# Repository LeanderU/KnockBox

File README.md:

# KnockBox

Want to stay in contact with your friends, family, or partner over long distances? The KnockBox was created to foster a sense of proximity to them. Instead of physically knocking on their door, you can knock on your box, and theirs will imitate your physical knocking. Additionally, the pair of identical boxes can exchange short audio messages, similar to Walkie Talkies.  

## How it works:

This project focuses on an interactive device that communicates with identical boxes, independent of their locations. The boxes are connected via the Internet, allowing them to exchange knocking sounds and audio messages. A servo imitates the physical knocking coming from a user of another box, while an LED indicates if a new audio message has been received. The user interface is limited to only one button that's used for playing the received audio message, recording a message, and sending it.

## Repository Contents:

1. **Docs**: Contains the Product Brief and Project Requirements.
2. **Electrical**: Includes schematics and PCB design files.
3. **Software**: Contains testing of submodules.

*Please note that the code of the final KnockBox and documentation on the hardware development are still under revision and have not yet been included in this repository.*

https://github.com/LeanderU/KnockBox/assets/84909019/8b67ddaa-3543-461e-bd95-6ebf5e21cfc9

The video shown only demonstrates the ability to record and play the knocking sound. The capability of recording and replaying audio messages is not implemented yet.

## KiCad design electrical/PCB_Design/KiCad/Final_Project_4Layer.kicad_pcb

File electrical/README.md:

After Assembly:

Screenshot from KiCad before the files were sent to the Manufacturer:

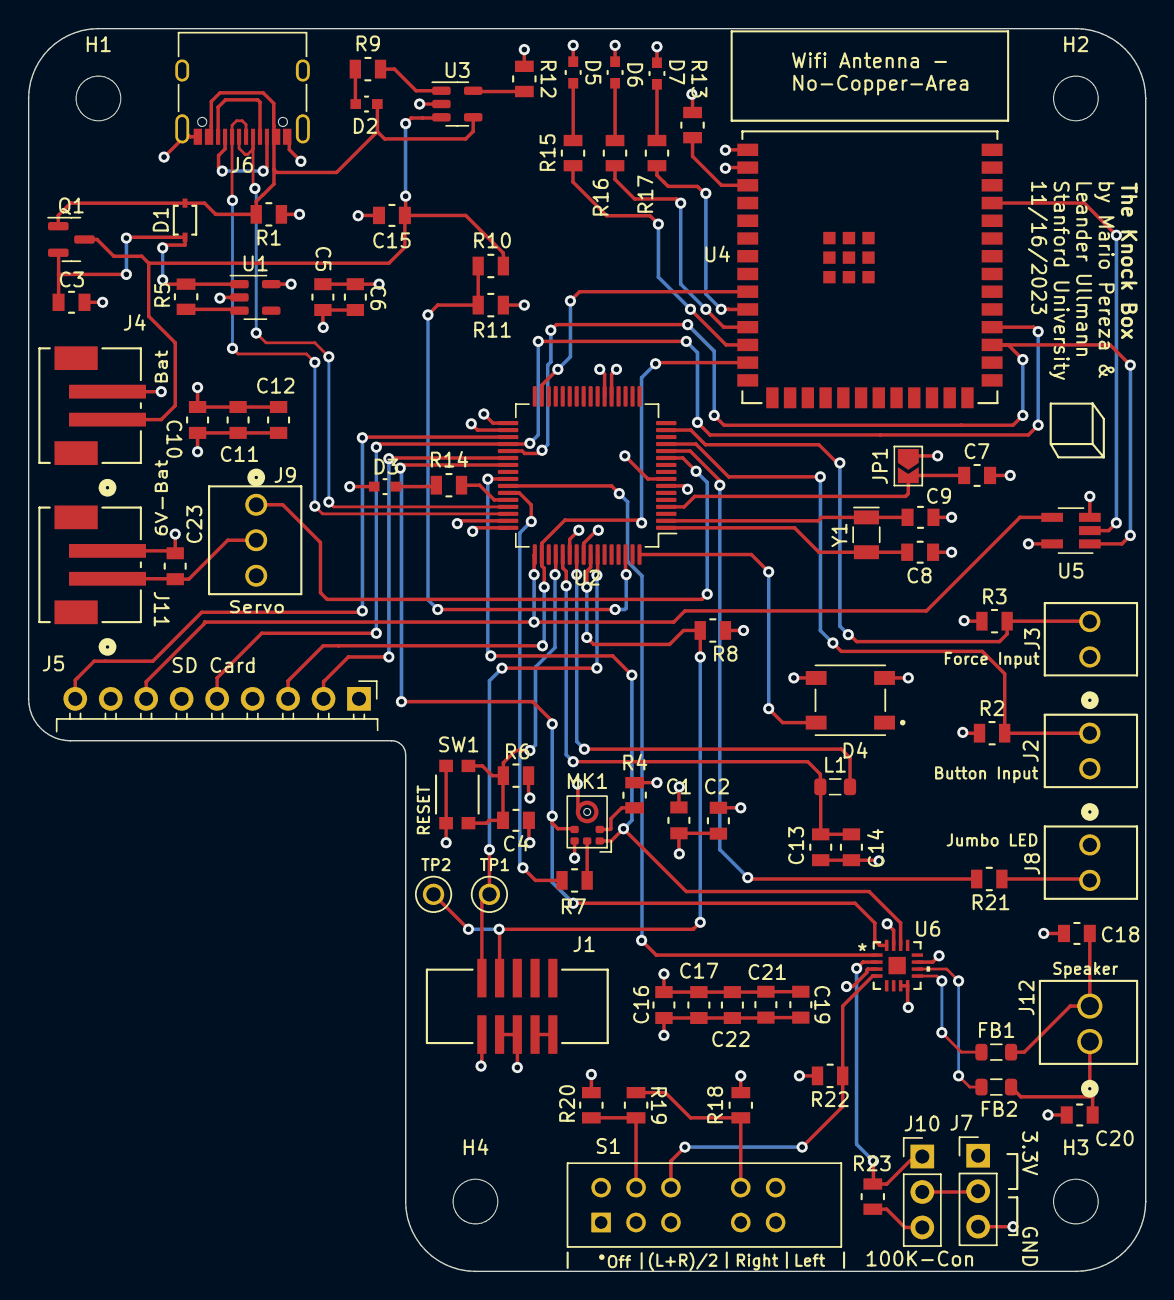
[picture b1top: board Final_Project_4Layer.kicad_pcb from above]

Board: 4 copper layers, 80.0 x 89.0 mm, 86 parts (0 on the bottom side), 60 nets.

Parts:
C1, C4, C6, C7, C11, C12, C13, C14: 1uF; G-21_MUR
C2, C18, C20: 220pF; G-21_MUR
C3, C5, C10, C15, C16, C19, C21, C22, C23: 10uF; G-21_MUR
C8, C9: 22pF; G-21_MUR
C17: 0.1uF; G-21_MUR
D1: D_Schottky; SDO_RB550VM-30TE-17_ROM
D2: ORANGE LED; LED_LTST-C191KRKT_LTO
D3, D6: RED LED; LED_LTST-C191KRKT_LTO
D4: NeoPixel_THT; LED_1655
D5: BLUE LED; LED_LTST-C191KRKT_LTO
D7: GREEN LED; LED_LTST-C191KRKT_LTO
FB1, FB2: FerriteBead; L_0805_2012Metric
H1, H2, H3, H4: MountingHole; MountingHole_3.2mm_M3_ISO7380
J1: 3221-10-0300-00; CONN10_3221-10-0300-00_CNC
J2, J3, J8: Molex2; CONN_22232021_MOL
J4, J11: B2B-PH-SM4-TB; CONN_B2B-PH-SM4-TBLFSN_JST
J5: 61300911021; PinHeader_1x09_P2.54mm_Horizontal
J6: USB_C_Receptacle_USB2.0; USB_C_Receptacle_XKB_U262-16XN-4BVC11
J7, J10: 61300311121; PinHeader_1x03_P2.54mm_Vertical
J9: Molex3; CONN3_22232031_MOL
J12: OSTVN02A150; CONN_OSTVN02A150_OST
JP1: SolderJumper-2_P1.3mm_Open_TrianglePad1.0x1.5mm
L1: 10uH; L_0805_2012Metric
MK1: SPH0645LM4H; Knowles_SPH0645LM4H-6_3.5x2.65mm
Q1: BSS84; SOT-23
R1, R10, R11, R23: 100K; STA_RMCF0805_STP
R2, R3, R4, R5, R6, R8, R12, R13: 10K; STA_RMCF0805_STP
R7: 68; STA_RMCF0805_STP
R9, R15, R16, R17, R20: 1K; STA_RMCF0805_STP
R14, R19, R21: 2.2K; STA_RMCF0805_STP
R18: 6.8K; STA_RMCF0805_STP
R22: 1M; STA_RMCF0805_STP
S1: SS-24E06-TG_5__P_; SW_SS-24E06-TG_5__P_
SW1: KMR231NG LFS; IC4_KMR231NGLFS_CNK
TP1, TP2: TestPoint; KEYSTONE_5000
U1: AP2112K-3.3; SOT-23-5
U2: ATSAMD51J19A-A; TQFP-64_10x10mm_P0.5mm
U3: MCP73831-2-OT; SOT-23-5
U4: ESP32-S3-WROOM-1-N16R8; ESP32­S3­WROOM­1U_EXP
U5: 74AHC1G125; SOT-23-5_HandSoldering
U6: MAX98357AETE+T; 21-0136I_T1633-4_MXM
Y1: Crystal; Crystal_SMD_MicroCrystal_CC7V-T1A-2Pin_3.2x1.5mm

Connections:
+3.3V: C1.1, C2.1, C5.1, C6.1, C10.1, C11.1, C12.1, C16.2, C17.2, C19.1, C21.1, C22.1, D4.3 (VDD), J1.6, J2.1, J3.1, J5.4, J7.1, JP1.1 (A), MK1.5 (VDD), R6.2, R8.1, R13.1, R18.2, R22.2, S1.6, U1.5 (VOUT), U2.8 (VDDANA), U2.21 (VDDIOB), U2.34 (VDDIO), U2.48 (VDDIO), U2.56 (VDDIO), U4.2 (VDD), U5.5 (VCC), U6.7 (VDD), U6.8 (VDD)
+6V: C23.1, J9.2, J11.1
+BATT: C15.2, J4.1, Q1.3 (D), R10.2, U3.3 (V_{BAT})
/AMPL_GAIN_SEL: J10.1, R23.1, U6.2 (GAIN_SLOT)
/AREF: C7.1, JP1.2 (B), U2.4 (PA03)
/Button_Signal: J2.2, R2.2, U2.13 (PA04)
/CS_Card: J5.2, U2.38 (PA19)
/CS_Wifi: U2.37 (PA18), U4.29 (IO5), U5.1
/Card_Detect: J5.9, U2.35 (PA16)
/ESP_Busy: U2.31 (PA14), U4.9 (IO33)
/Force_Signal: J3.2, R3.2, U2.15 (PA06)
/I2S_BCLK: MK1.4 (BCLK), U2.39 (PB16), U6.16 (BCLK)
/I2S_DIN: U2.42 (PA21), U6.1 (DIN)
/I2S_DOUT: R7.1, U2.43 (PA22)
/I2S_LRCLK: MK1.1 (WS), U2.41 (PA20), U6.14 (LRCLK)
/MISO: J5.7, U2.49 (PB22), U5.4
/MISO_ESP: U4.37 (IO23), U5.2
/MOSI: J5.3, U2.50 (PB23), U4.13 (IO14)
/SCK: J5.5, U2.36 (PA17), U4.30 (IO18)
/SD_MODE: R22.1, S1.8, U6.4 (*SD_MODE)
/SWCLK: J1.2, R8.2, TP2.TP (1), U2.57 (PA30)
/SWDIO: J1.1, TP1.TP (1), U2.58 (PA31)
/VO+: FB2.1, U6.10 (OUTN)
/VO-: FB1.1, U6.9 (OUTP)
/V_DIV: R10.1, R11.2, U2.62 (PB01)
D8_NEOPIX: D4.4 (DIN), U2.64 (PB03)
D+: J6.A6 (D+), J6.B6 (D+), U2.46 (PA25)
D-: J6.A7 (D-), J6.B7 (D-), U2.45 (PA24)
ESP_BLUE: R15.1, U4.12 (IO27)
ESP_GREEN: R17.1, U4.10 (IO25)
ESP_RED: R16.1, U4.11 (IO26)
GND: C1.2, C2.2, C3.2, C4.2, C5.2, C6.2, C7.2, C8.1, C9.1, C10.2, C11.2, C12.2, C13.1, C14.1, C15.1, C16.1, C17.1, C18.2, C19.2, C20.2, C21.2, C22.2, C23.2, D3.1 (K), D4.2 (GND), D5.1 (K), D6.1 (K), D7.1 (K), J1.7, J1.8, J4.2, J5.6, J6.A1 (GND), J6.A12 (GND), J6.B1 (GND), J6.B12 (GND), J6.S1 (SHIELD), J7.3, J8.2, J9.3, J11.2, MK1.3 (GND), R1.1, R2.1, R3.1, R4.1, R11.1, R12.1, R20.2, S1.10, SW1.1, SW1.3, U1.2 (GND), U2.7 (GNDANA), U2.22 (GND), U2.33 (GND), U2.47 (GND), U2.54 (GND), U3.2 (V_{SS}), U4.1 (GND), U5.3 (GND), U6.3 (GND), U6.11 (GND), U6.15 (GND)
JUMBO_LED: R21.1, U2.12 (PB09)
unnamed: C18.1, FB1.2, J12.2
unnamed: C20.1, FB2.2, J12.1
unnamed: C3.1, D1.1 (K), Q1.2 (S), R5.2, U1.1 (VIN)
unnamed: D2.1 (K), R9.2
unnamed: D3.2 (A), R14.2
unnamed: D5.2 (A), R15.2
unnamed: D6.2 (A), R16.2
unnamed: D7.2 (A), R17.2
unnamed: J8.1, R21.2
unnamed: J7.2, J10.2
unnamed: J10.3, R23.2
unnamed: MK1.6 (DATA), R7.2
unnamed: MK1.2 (SEL), R4.2
unnamed: R18.1, R19.1, S1.7
unnamed: R19.2, R20.1, S1.9
unnamed: R5.1, U1.3 (EN)
unnamed: C8.2, U2.1 (PA00), Y1.2
unnamed: C9.2, U2.2 (PA01), Y1.1
unnamed: C13.2, C14.2, L1.1, U2.53 (VDDCORE)
unnamed: L1.2, U2.55 (VSW)
unnamed: R12.2, U3.5 (PROG)
unnamed: R9.1, U3.1 (STAT)
unnamed: R13.2, U4.3 (EN)
PWM_Servo: J9.1, U2.11 (PB08)
RED_LED: R14.1, U2.44 (PA23)
RESET: C4.1, R6.1, SW1.2, SW1.4, U2.52 (~RESET)
VBUS: D1.2 (A), D2.2 (A), J6.A4 (VBUS), J6.A9 (VBUS), J6.B4 (VBUS), J6.B9 (VBUS), Q1.1 (G), R1.2, U3.4 (V_{DD})

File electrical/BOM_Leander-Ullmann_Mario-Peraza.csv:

BOM - Knock Box,,,,,,,,,,,,,,,
Note: Quantities in red refer to two boxes (one for Mario and one for Leander) plus some reasonable buffer.,,,,,,,,,,,,,,,
#,Sourced,Placed,References,Value,Footprint,MFR,MFR Part Number,Supplier 1,Supplier 1 Part Number,URL, $ per Unit ,Quantity single Box,$ per categorie per box,Quantity to Order (two Boxes plus buffer),$ per categorie for both boxes plus buffer
1,,,"C3, C5, C10, C15, C16, C19, C21, C22, C23",10uF,G-21_MUR,Murata Electronics,GRM21BR61C106KE15K,DigiKey,490-6473-1-ND,,$0.18 ,9,$1.62 ,22,$3.96 
2,,,"C1, C4, C6, C7, C11, C12, C13, C14",1uF,G-21_MUR,Murata Electronics,GRM21BR71C105KA01L,DigiKey,490-1691-1-ND,,$0.21 ,8,$1.68 ,20,$4.20 
3,,,"C2, C18, C20",220pF,G-21_MUR,Murata Electronics,GRM21A5C2E221JW01D,DigiKey,490-13371-1-ND,,$0.25 ,3,$0.75 ,10,$2.50 
4,,,"C8, C9",22pF,G-21_MUR,Murata Electronics,GRM21A5C2D220JW01D,DigiKey,490-14650-1-ND,,$0.25 ,2,$0.50 ,8,$2.00 
5,,,C17,0.1uF,G-21_MUR,Murata Electronics,GRM21B7U1A104JA01L,DigiKey,490-11592-1-ND,,$0.32 ,1,$0.32 ,6,$1.92 
6,,,"R2, R3, R4, R5, R6, R8, R12, R13",10K,STA_RMCF0805_STP,Stackpole Electronics Inc,RMCF0805FT10K0,DigiKey,RMCF0805FT10K0CT-ND,,$0.10 ,8,$0.80 ,20,$2.00 
7,,,"R9, R15, R16, R17, R20",1K,STA_RMCF0805_STP,Stackpole Electronics Inc,RMCF0805FT1K00,DigiKey,RMCF0805FT1K00CT-ND,,$0.10 ,5,$0.50 ,14,$1.40 
8,,,"R1, R10, R11, R23",100K,STA_RMCF0805_STP,Stackpole Electronics Inc,RMCF0805FT100K,DigiKey,RMCF0805FT100KCT-ND,,$0.10 ,4,$0.40 ,12,$1.20 
9,,,"R14, R19, R21",2.2K,STA_RMCF0805_STP,Stackpole Electronics Inc,RMCF0805FT2K20,DigiKey,RMCF0805FT2K20CT-ND,,$0.10 ,3,$0.30 ,10,$1.00 
10,,,R7,68,STA_RMCF0805_STP,Stackpole Electronics Inc,RMCF0805JT68R0,DigiKey,RMCF0805JT68R0CT-ND,,$0.10 ,1,$0.10 ,4,$0.40 
11,,,R18,6.8K,STA_RMCF0805_STP,Stackpole Electronics Inc,RMCF0805FT6K80,DigiKey,RMCF0805FT6K80CT-ND,,$0.10 ,1,$0.10 ,4,$0.40 
12,,,R22,1M,STA_RMCF0805_STP,Stackpole Electronics Inc,RMCF0805JT1M00,DigiKey,RMCF0805JT1M00CT-ND,,$0.10 ,1,$0.10 ,4,$0.40 
13,,,L1,10uH,L_0805_2012Metric,Bourns Inc.,CV201210-100K,DigiKey,CV201210-100KCT-ND,,$0.10 ,1,$0.10 ,4,$0.40 
14,,,"D3, D6",RED LED,LED_LTST-C191KRKT_LTO,Lite-On Inc.,LTST-C191KRKT,DigiKey,160-1447-1-ND,,$0.25 ,2,$0.50 ,6,$1.50 
15,,,D1,D_Schottky,SDO_RB550VM-30TE-17_ROM,Rohm Semiconductor,RB550VM-30TE-17,DigiKey,846-RB550VM-30TE-17CT-ND,,$0.38 ,1,$0.38 ,4,$1.52 
16,,,D2,ORANGE LED,LED_LTST-C191KRKT_LTO,Lite-On Inc.,LTST-C191KFKT,DigiKey,160-1445-1-ND,,$0.23 ,1,$0.23 ,4,$0.92 
17,,,D4,NeoPixel_THT,LED_1655,Adafruit Industries LLC,1655,DigiKey,1528-1104-ND,,$4.50 ,1,$4.50 ,4,$18.00 
18,,,D5,BLUE LED,LED_LTST-C191KRKT_LTO,Lite-On Inc.,LTST-C191TBKT,DigiKey,160-1647-1-ND,,$0.34 ,1,$0.34 ,4,$1.36 
19,,,D7,GREEN LED,LED_LTST-C191KRKT_LTO,Lite-On Inc.,LTST-C191KGKT,DigiKey,160-1446-1-ND,,$0.25 ,1,$0.25 ,4,$1.00 
20,,,U1,AP2112K-3.3,SOT-23-5,Diodes Incorporated,AP2112K-3.3TRG1,DigiKey,AP2112K-3.3TRG1DICT-ND,,$0.35 ,1,$0.35 ,3,$1.05 
21,,,U2,ATSAMD51J19A-A,TQFP-64_10x10mm_P0.5mm,Microchip Technology,ATSAMD51J19A-AUT,DigiKey,ATSAMD51J19A-AUTCT-ND,,$5.68 ,1,$5.68 ,3,$17.04 
22,,,U3,MCP73831-2-OT,SOT-23-5,Microchip Technology,MCP73831T-2ACI/OT,DigiKey,MCP73831T-2ACI/OTCT-ND,,$0.76 ,1,$0.76 ,3,$2.28 
23,,,U4,ESP32-S3-WROOM-1-N16R8,ESP32Â­S3Â­WROOMÂ­1U_EXP,Espressif Systems,ESP32-S3-WROOM-1-N16R8,DigiKey,1965-ESP32-S3-WROOM-1-N16R8CT-ND,,$2.95 ,1,$2.95 ,3,$8.85 
24,,,U5,74AHC1G125,USB_C_Receptacle_XKB_U262-16XN-4BVC11,Texas Instruments,SN74AHC1G125DBVR,DigiKey,296-8744-1-ND,,$0.37 ,1,$0.37 ,3,$1.11 
25,,,U6,MAX98357AETE+T,21-0136I_T1633-4_MXM,Analog Devices Inc./Maxim Integrated,MAX98357AETE+T,DigiKey,MAX98357AETE+TCT-ND,,$2.89 ,1,$2.89 ,3,$8.67 
26,,,Y1,Crystal,Crystal_SMD_MicroCrystal_CC7V-T1A-2Pin_3.2x1.5mm,ECS Inc.,ECS-.327-12.5-34B-TR,DigiKey,XC1617CT-ND,,$0.44 ,1,$0.44 ,4,$1.76 
27,,,SW1,KMR231NG LFS,IC4_KMR231NGLFS_CNK,,KMR231NG LFS,DigiKey,CKN10246CT-ND,,$0.64 ,1,$0.64 ,4,$2.56 
28,,,"H1, H2, H3, H4",MountingHole,MountingHole_3.2mm_M3_ISO7380,,,,,,,4, $-   ,0, $-   
29,,,"FB1, FB2",FerriteBead,L_0805_2012Metric,Laird-Signal Integrity Products,HI0805Q310R-10,DigiKey,240-2394-1-ND,,$0.20 ,2,$0.40 ,6,$1.20 
30,,,"TP1, TP2",TestPoint,KEYSTONE_5000,Keystone Electronics,5000,DigiKey,36-5000-ND,,$0.38 ,2,$0.76 ,6,$2.28 
31,,,JP1,~,SolderJumper-2_P1.3mm_Open_TrianglePad1.0x1.5mm,,,,,,,1, $-   ,0, $-   
32,,,MK1,SPH0645LM4H,Knowles_SPH0645LM4H-6_3.5x2.65mm,Knowles,SPH0645LM4H-B,DigiKey,423-SPH0645LM4H-BCT-ND,,$2.74 ,1,$2.74 ,4,$10.96 
33,,,Q1,BSS84,SOT-23,Diodes Incorporated,BSS84-7-F,DigiKey,BSS84-FDICT-ND,,$0.24 ,1,$0.24 ,3,$0.72 
34,,,S1,SS-24E06-TG_5__P_,SW_SS-24E06-TG_5__P_,C&K,SS-24E06-TG 5 (P),DigiKey,CKN10394-ND,,$1.15 ,1,$1.15 ,3,$3.45 
35,,,"J2, J3, J8",Molex2,CONN_22232021_MOL,Molex,22232021,DigiKey,900-0022232021-ND,,$0.21 ,3,$0.63 ,8,$1.68 
36,,,"J4, J11",B2B-PH-SM4-TB,CONN_B2B-PH-SM4-TBLFSN_JST,JST Sales America Inc.,B2B-PH-SM4-TB,DigiKey,455-B2B-PH-SM4-TBCT-ND,,$0.55 ,2,$1.10 ,6,$3.30 
37,,,"J7, J10",61300311121,PinHeader_1x03_P2.54mm_Vertical,WÃ¼rth Elektronik,61300311121,DigiKey,732-5316-ND,,$0.13 ,2,$0.26 ,6,$0.78 
38,,,J1,3221-10-0300-00,CONN10_3221-10-0300-00_CNC,CNC Tech,3221-10-0300-00,DigiKey,1175-1735-ND,,$0.76 ,1,$0.76 ,3,$2.28 
39,,,J5,61300911021,PinHeader_1x09_P2.54mm_Horizontal,WÃ¼rth Elektronik,61300911021,DigiKey,732-5342-ND,,$0.88 ,1,$0.88 ,3,$2.64 
40,,,J6,USB_C_Receptacle_USB2.0,USB_C_Receptacle_XKB_U262-16XN-4BVC11,XKB Connectivity,U262-161N-4BVC11,LCSC ELECTRONICS,C319148,,$0.40 ,1,$0.40 ,3,$1.20 
41,,,J9,Molex3,CONN3_22232031_MOL,Molex,22232031,DigiKey,WM4201-ND,,$0.27 ,1,$0.27 ,3,$0.81 
42,,,J12,OSTVN02A150,CONN_OSTVN02A150_OST,On Shore Technology Inc.,OSTVN02A150,DigiKey,ED10561-ND,,$1.08 ,1,$1.08 ,3,$3.24 
43,,,not part of PCB,Force Sensor,,Adafruit Industries LLC,1075,Adafruit Industries LLC,1075,,$5.95 ,1,$5.95 ,2,$11.90 
44,,,not part of PCB,Jumbo LED Green,,Kingbright,WP813GD,DigiKey,754-1898-ND,,$0.43 ,1,$0.43 ,2,$0.86 
45,,,not part of PCB,Jumbo LED Red,,Kingbright,WP813SURDK,DigiKey,754-WP813SURDK-ND,,$0.62 ,0, $-   ,2,$1.24 
46,,,not part of PCB,6V Servo Motor,,Parallax Inc.,900-00005,DigiKey,900-00005-ND,,$15.87 ,1,$15.87 ,2,$31.74 
47,,,not part of PCB,16mm Flush Button,,-,-,Ebay,1.31657E+11,https://www.ebay.com/itm/131657180740,$5.99 ,1,$5.99 ,2,$11.98 
48,,,not part of PCB,SD-Card-Module,,Adafruit Industries LLC,4682,DigiKey,1528-4682-ND,,$3.50 ,1,$3.50 ,3,$10.50 
49,,,not part of PCB,Jumper Pin Shunts,,Sullins Connector Solutions,STC02SYAN,DigiKey,S9000-ND,,$0.10 ,2,$0.20 ,6,$0.60 
50,,,not part of PCB,Female Socket Angled,,Sullins Connector Solutions,PPPC091LGBN-RC,DigiKey,S5484-ND,,$0.77 ,1,$0.77 ,2,$1.54 
51,,,not part of PCB,Male Header Angled,,Würth Elektronik,61300911021,DigiKey,732-5342-ND,,$0.88 ,1,$0.88 ,2,$1.76 
52,,,not part of PCB,Molex Crimp Housing 2 Pins,,Molex,22013027,DigiKey,900-0022013027-ND,,$0.16 ,3,$0.48 ,10,$1.60 
53,,,not part of PCB,Molex Crimp Housing 3 Pins,,Molex,22013037,DigiKey,900-0022013037-ND,,$0.19 ,1,$0.19 ,3,$0.57 
54,,,not part of PCB,Crimp Terminals,,Molex,8650804,DigiKey,WM2756CT-ND,,$0.10 ,9,$0.90 ,30,$3.00 
55,,,not part of PCB,Battery Pack,,Adafruit Industries LLC,3859,DigiKey,1528-2707-ND,,$2.95 ,1,$2.95 ,2,$5.90 
56,,,not part of PCB,AA Batteries,,Panasonic - BSG,LR6XWA/BXU,DigiKey,11-LR6XWA/BXU-ND,,$0.44 ,4,$1.76 ,8,$3.52 
57,,,not part of PCB,Lithion Battery 3.7V,,SparkFun Electronics,PRT-13855,DigiKey,1568-1686-ND,,$13.95 ,1,$13.95 ,2,$27.90 
,,,,SD Card,,,,,,,,,$92.04 ,,$238.55 
,,,,Speaker,,,,,,,,,,,

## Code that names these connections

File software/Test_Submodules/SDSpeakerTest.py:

import board
import time
import audioio
# new imports for the SD card
import busio
import digitalio
import storage
import adafruit_sdcard  # add this library
from audiocore import WaveFile

# The SD card uses a protocol called SPI.  We'll see much more of this very soon.
# For now, what we need is a digital line to select the SD card (cs, below), and
# connections for the SPI signal lines to the SD card (spi, below)

# Use a digital pin to select the SD card
cs = digitalio.DigitalInOut(board.PA19)
# Wire up the SPI pins
spi = busio.SPI(board.PA17, board.PB23, board.PB22)

# Connect to the card and mount the filesystem.
# Once this is done, the SD card looks just like another part of the files system!
sdcard = adafruit_sdcard.SDCard(spi, cs)
vfs = storage.VfsFat(sdcard)
storage.mount(vfs, "/sd")

wave_file = open("/sd/AUDIO/example.wav", "rb") # Note the "/sd/" prefix for the SD card
wave = WaveFile(wave_file)            # Everything else is the same ...
audio = audioio.AudioOut(board.PA02)
audio.play(wave)
time.sleep(10)

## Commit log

2024-04-22 Create doc folder
2024-04-22 Create folder electrical
2024-04-22 Create software folder
2024-04-22 Create BOM folder
2024-04-22 Add BOM files
2024-04-22 Create BuildCircuitPython folder
2024-04-22 Create PCB_Design folder
2024-04-22 Create Files_for_manufacturer folder
2024-04-22 Create KiCAD folder
